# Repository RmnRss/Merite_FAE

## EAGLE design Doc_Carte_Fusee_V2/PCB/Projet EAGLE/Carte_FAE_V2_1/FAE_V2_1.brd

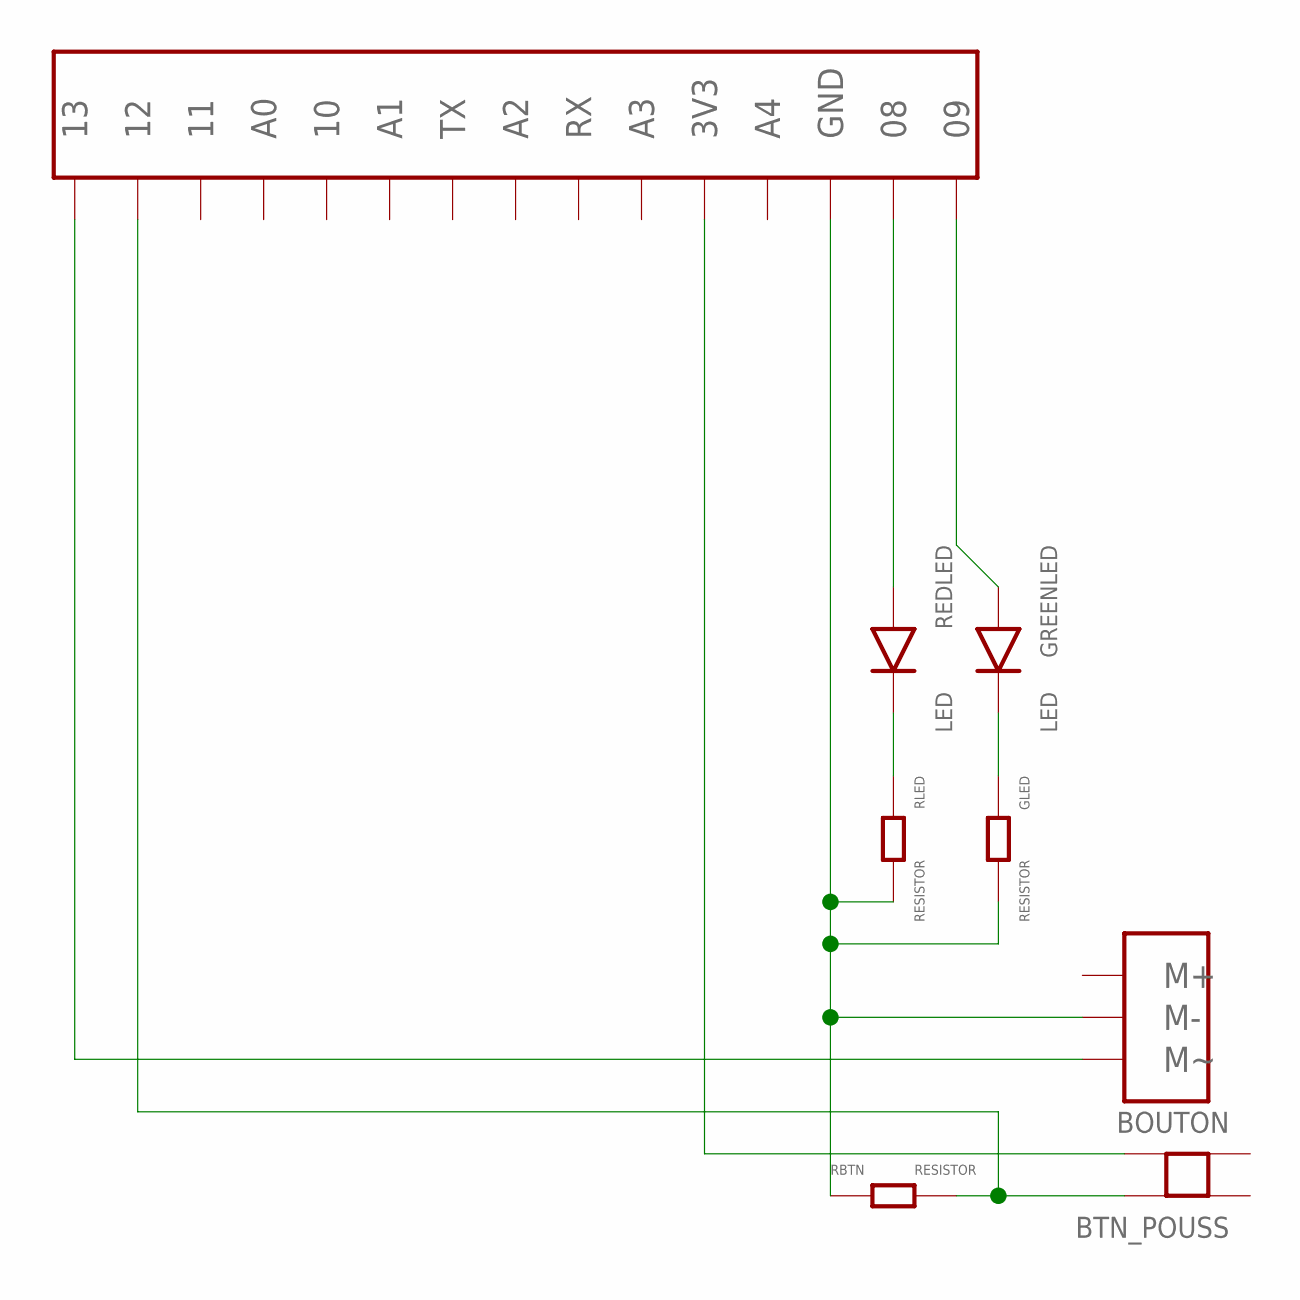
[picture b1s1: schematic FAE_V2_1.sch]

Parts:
BTN_POUSS: BOUTON
GLED: RESISTOR
GREENLED: LED
RBTN: RESISTOR
REDLED: LED
RLED: RESISTOR
U$1: RAZOR_BOARD
U$3: SERVO_ADAPT

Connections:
unnamed: GREENLED.IN, U$1.09
unnamed: GLED.A, GREENLED.OUT
unnamed: BTN_POUSS.D, U$1.3V3
unnamed: BTN_POUSS.C, RBTN.B, U$1.12
unnamed: U$1.13, U$3.M~
unnamed: GLED.B, RBTN.A, RLED.B, U$1.GND, U$3.M-
unnamed: REDLED.IN, U$1.08
unnamed: REDLED.OUT, RLED.A

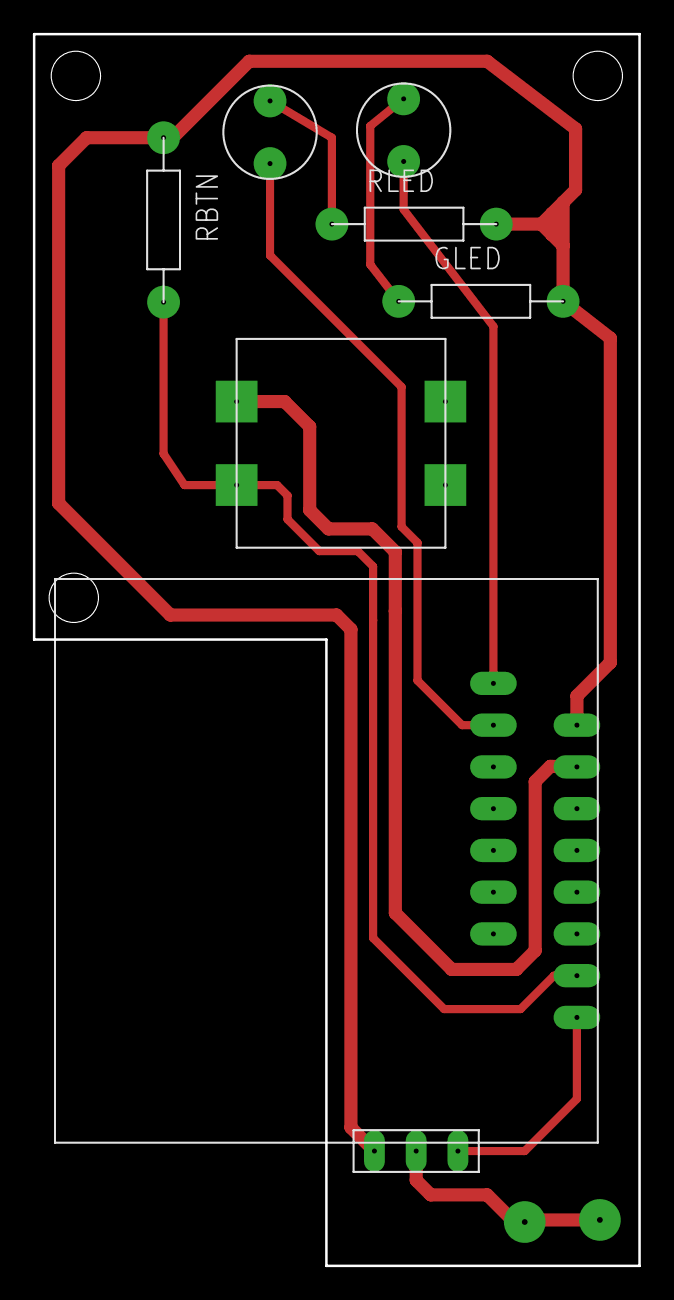
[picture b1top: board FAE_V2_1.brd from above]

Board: 2 copper layers, 36.8 x 74.9 mm, 8 parts (0 on the bottom side), 8 nets.

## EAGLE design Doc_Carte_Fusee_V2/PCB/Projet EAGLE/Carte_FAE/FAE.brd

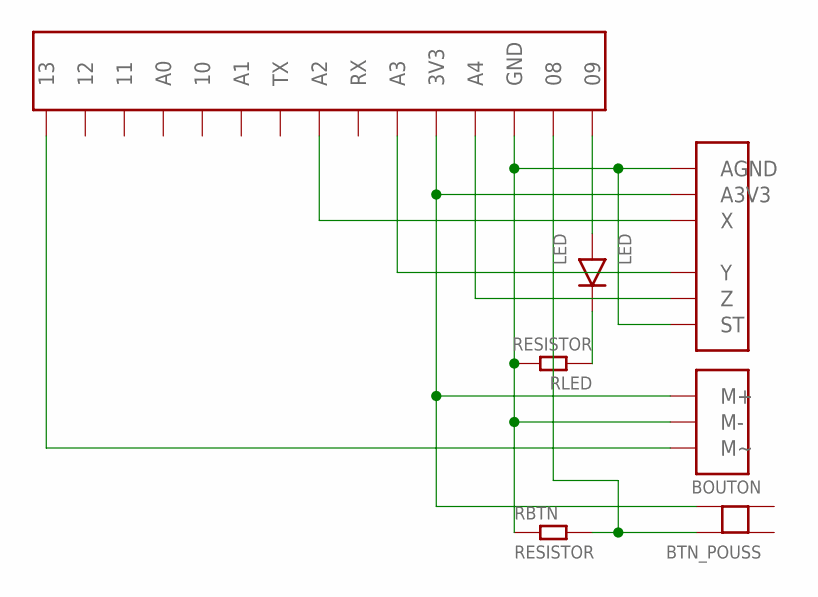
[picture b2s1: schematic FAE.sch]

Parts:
BTN_POUSS: BOUTON
LED: LED
RBTN: RESISTOR
RLED: RESISTOR
U$1: RAZOR_BOARD
U$2: ADXL377
U$3: SERVO_ADAPT

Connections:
unnamed: LED.IN, U$1.09
unnamed: LED.OUT, RLED.A
unnamed: RBTN.A, RLED.B, U$1.GND, U$2.AGND, U$2.ST, U$3.M-
unnamed: BTN_POUSS.D, U$1.3V3, U$2.A3.3V (A3V3), U$3.M+
unnamed: BTN_POUSS.C, RBTN.B, U$1.08
unnamed: U$1.13, U$3.M~
unnamed: U$1.A2, U$2.X
unnamed: U$1.A3, U$2.Y
unnamed: U$1.A4, U$2.Z

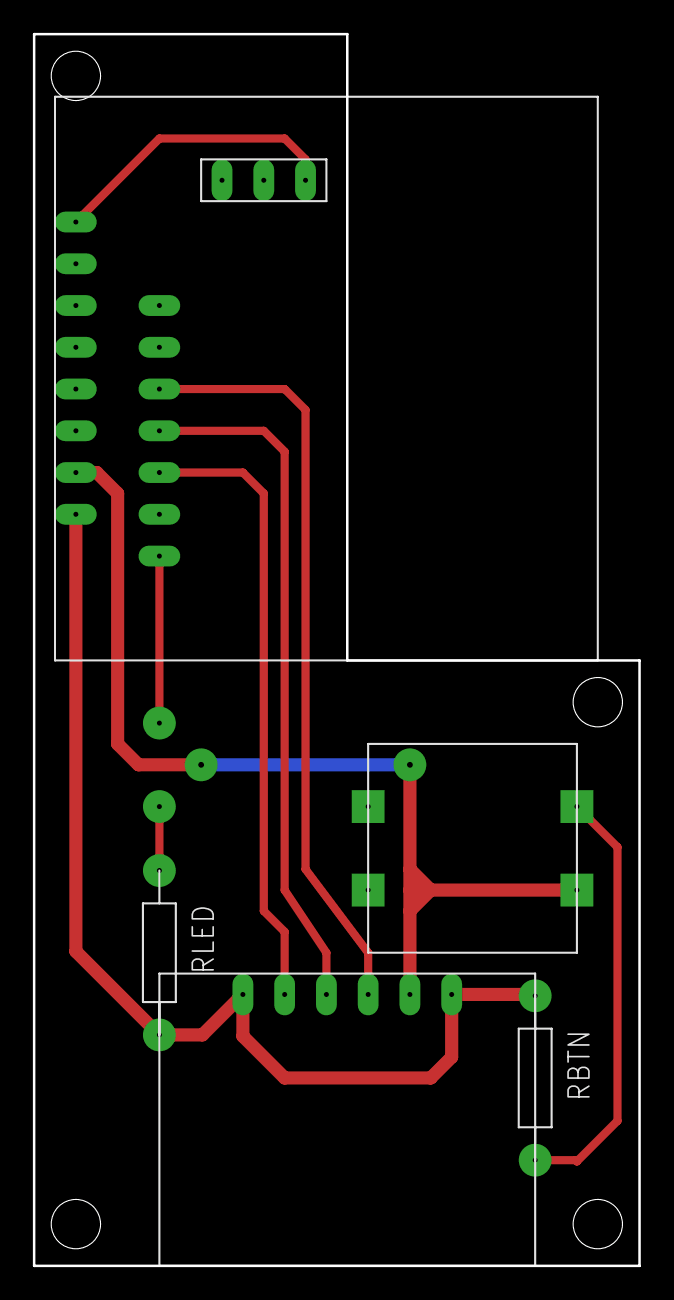
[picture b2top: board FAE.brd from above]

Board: 2 copper layers, 36.8 x 74.9 mm, 7 parts (0 on the bottom side), 9 nets.

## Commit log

2018-02-27 First push
    27/02/2018
2018-02-27 Suppression fichiers inutiles
2018-03-01 Dernière Version
2018-06-28 Nettoyage Update Ajouts
2018-06-28 Cleaning
2018-07-03 Modification du code et du typon
2018-07-11 Ajouts 11/07
    Code BME_ONLY
    Fichiers Lancers
    Exploitation en Python
2018-07-13 Fin_Stage
    Fusée Altimètre Seul
    Ajout Python
    Exe Non fonctionnel
2018-09-12 Clean code
    Exploitation des données sans vitesse
